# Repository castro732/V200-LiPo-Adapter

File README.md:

# V200 LiPo Adapter

## Description

This is a boost converter, using a MAX631 with 5V preset. It has a Low Battery LED which will turn on at around 2.6 V.

I made this specifically to use a 1 Cell LiPo to step-up 3.7V to 5V to be used in Texas Voyage 200 Calculator.

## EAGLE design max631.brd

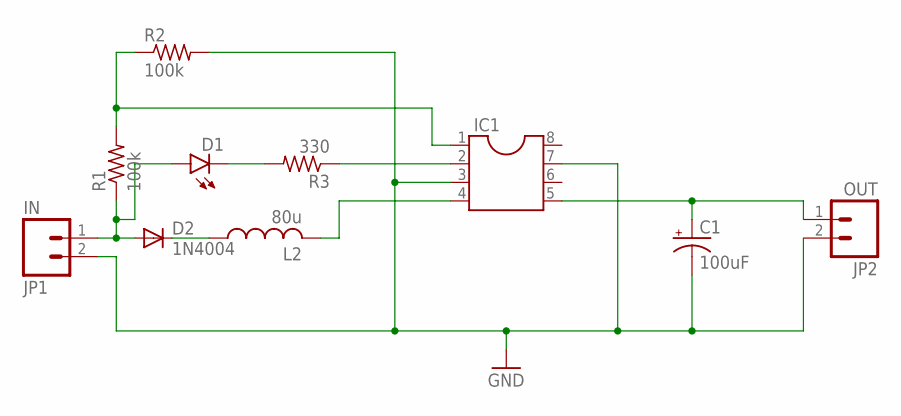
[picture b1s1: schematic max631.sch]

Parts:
C1: 100uF; E2,5-5
D1: LED3MM
D2: 1N4004; DO41-10
IC1: DIL8; DIL08
JP1: IN; 1X02_LOCK_LONGPADS
JP2: OUT; 1X02_LOCK_LONGPADS
L2: 80u; IR-2
R1, R2: 100k; 0207/10
R3: 330; 0207/10

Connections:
GND: C1.-, IC1.3, IC1.7, JP1.2, JP2.2, R2.2
unnamed: D1.A, D2.A, JP1.1, R1.1
unnamed: D2.C, L2.1
unnamed: IC1.1, R1.2, R2.1
unnamed: C1.+, IC1.5, JP2.1
unnamed: D1.K (C), R3.2
unnamed: IC1.4, L2.2
unnamed: IC1.2, R3.1

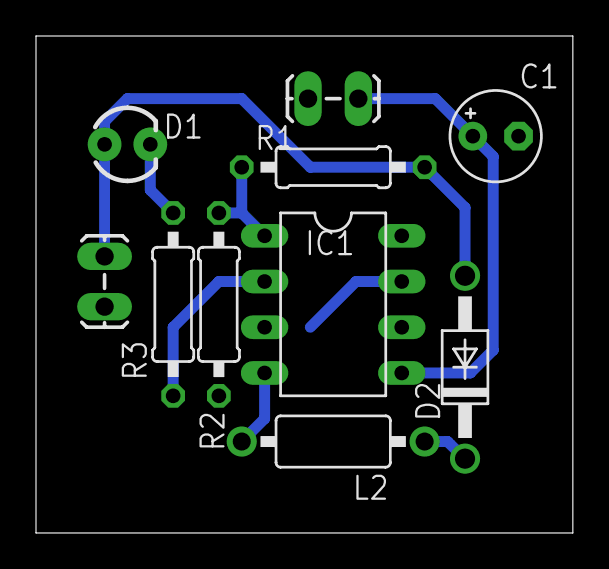
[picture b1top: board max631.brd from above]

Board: 2 copper layers, 29.8 x 27.6 mm, 10 parts (0 on the bottom side), 8 nets.

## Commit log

2016-05-03 Add files

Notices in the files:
parts and their libraries:
SparkFun-Connectors: Licensing: Creative Commons ShareAlike 4.0 International - https://creativecommons.org/licenses/by-sa/4.0
